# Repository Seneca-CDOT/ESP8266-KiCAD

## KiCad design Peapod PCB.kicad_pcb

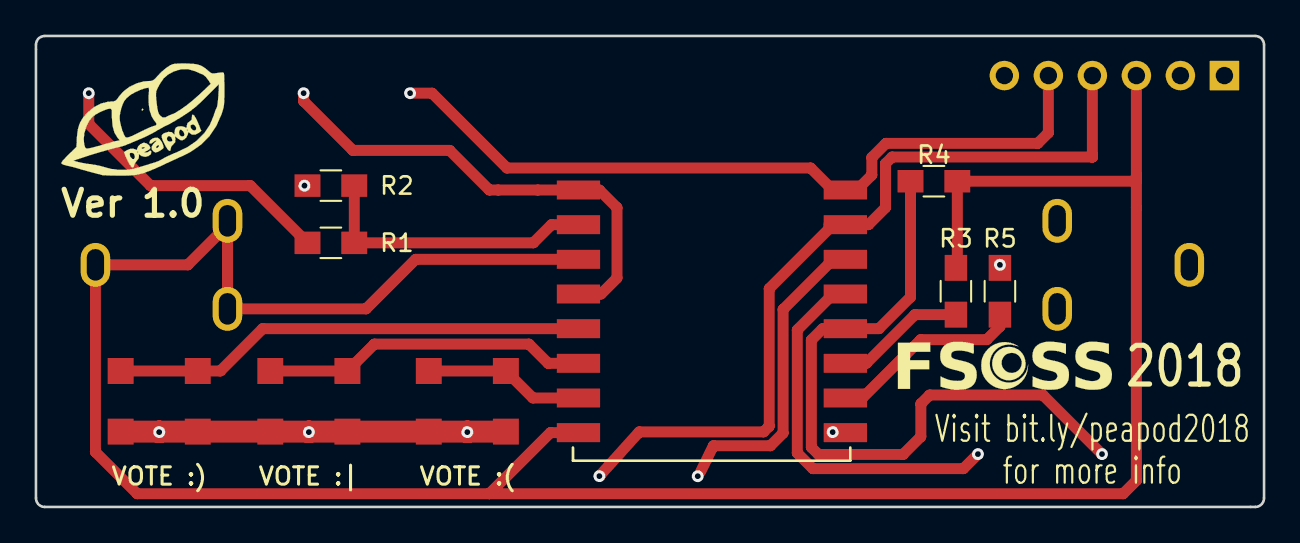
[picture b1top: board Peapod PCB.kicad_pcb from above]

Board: 2 copper layers, 70.9 x 27.2 mm, 18 parts (1 on the bottom side), 15 nets.

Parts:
ANALOG: CONN_01X01; Alligator Pad
BT1: Battery_Cell; BatteryMount
FTDI 3.3V Vcc ONLY!: CONN_01X06; Pin_Header_Straight_1x06_Pitch2.54mm
GND   GPIO0: CONN_01X02; Bridge Pad
GPIO4, GPIO5: CONN_01X01; Alligator Pad
R1: 25k; R_0805_HandSoldering
R2, R3, R4, R5: 10k; R_0805_HandSoldering
RESET   GND: CONN_01X02; Bridge Pad
RX: CONN_01X01; Alligator Pad
TX: CONN_01X01; Alligator Pad
U1: ESP8266; ESP-12E_SMD
VOTE :(: Pushbutton
VOTE :): Pushbutton
VOTE :|: Pushbutton

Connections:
+3V3: BT1.1, FTDI 3.3V Vcc ONLY!.3, R3.1, R4.2, U1.3, U1.8
GND: BT1.2, FTDI 3.3V Vcc ONLY!.1, GND GPIO0.2, R2.2, R5.2, RESET GND.2, U1.9, VOTE :(.1, VOTE :).1, VOTE :|.1
unnamed: U1.6, VOTE :|.2
unnamed: U1.5, VOTE :).2
unnamed: U1.7, VOTE :(.2
unnamed: ANALOG.1, R1.2
unnamed: RESET GND.1, U1.1, U1.4
unnamed: FTDI 3.3V Vcc ONLY!.4, RX.1, U1.15
unnamed: FTDI 3.3V Vcc ONLY!.5, TX.1, U1.16
unnamed: GPIO5.1, U1.14
unnamed: GPIO4.1, U1.13
unnamed: GND GPIO0.1, R4.1, U1.12
unnamed: R1.1, R2.1, U1.2
unnamed: R3.2, U1.11
unnamed: R5.1, U1.10

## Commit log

2018-05-29 Updated logo, year, names
